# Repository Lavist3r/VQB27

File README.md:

# VQB27
Small project for controlling two seven-segment displays (VQB27) with an Arduino Nano.

# About VQB27

This project utilizes two VQB27 seven-segment displays. Information on the VQB27 is really tight, only thing know about it is that it was manufactured in the GDR.

# Introduction

The VQB27, a SS126 NPN and an Arduino Nano were used in  this project. A custom PCB was designed and manufactured to have a somewhat functional two digit display thats also decent looking and not like a bomb on a breadboard.

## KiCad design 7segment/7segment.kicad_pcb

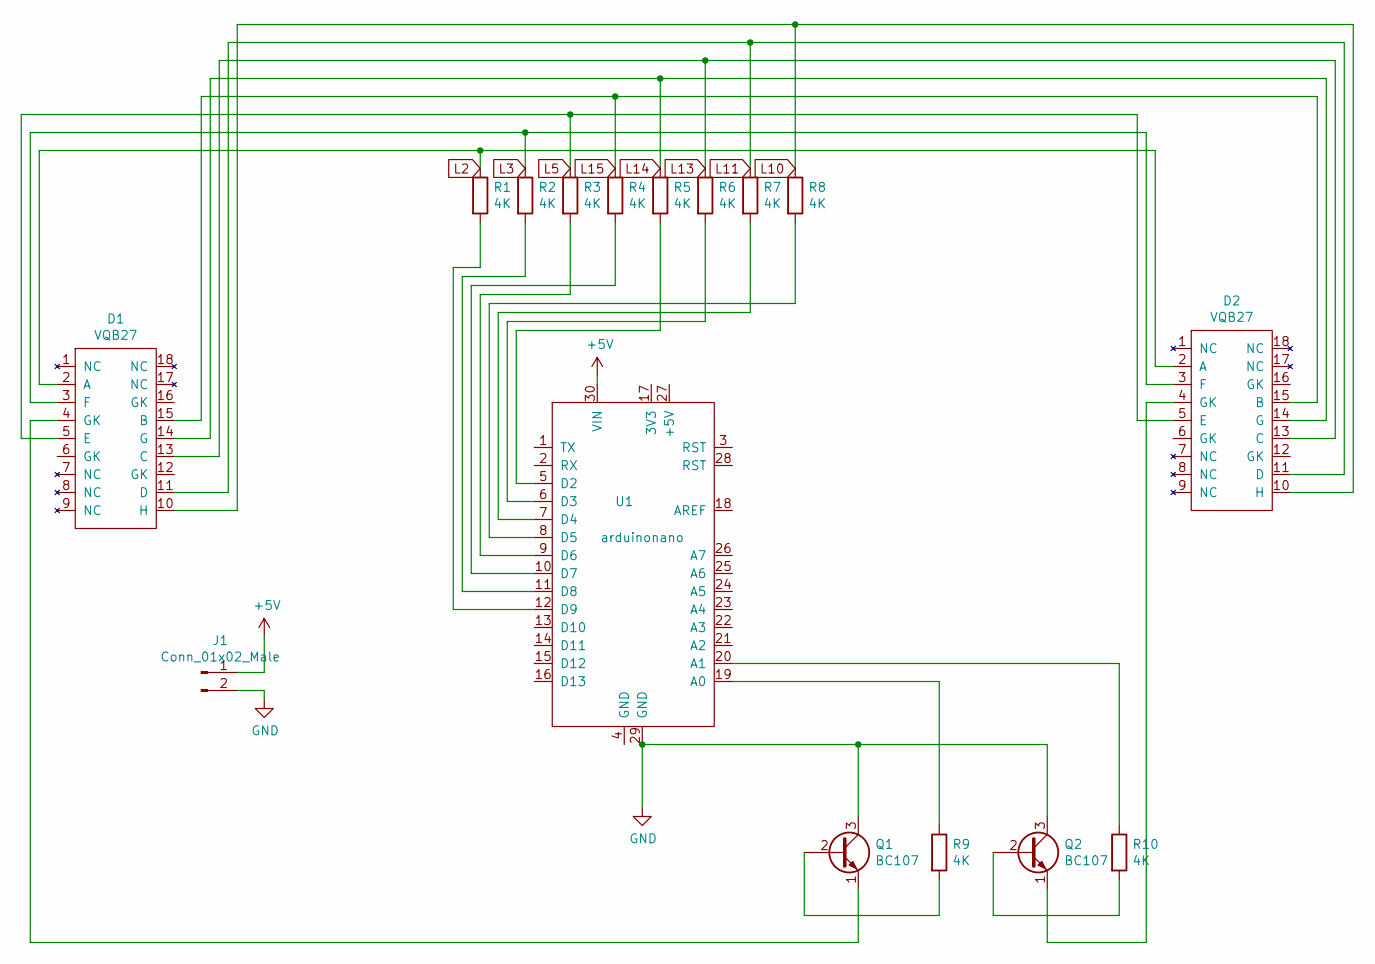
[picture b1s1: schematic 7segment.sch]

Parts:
D1, D2: VQB27
J1: Conn_01x02_Male; PinHeader_1x02_P1.00mm_Horizontal
Q1, Q2: BC107; TO-39-3
R1, R2, R3, R4, R5, R6, R7, R8, R9, R10: 4K; R_Axial_DIN0207_L6.3mm_D2.5mm_P2.54mm_Vertical
U1: arduinonano; Arduino_Nano

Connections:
+5V: J1.1, U1.30 (VIN)
GND: J1.2, Q1.3 (C), Q2.3 (C), U1.29 (GND)
L2: D1.2 (A), D2.2 (A), R1.1
L3: D1.3 (F), D2.3 (F), R2.1
L5: D1.5 (E), D2.5 (E), R3.1
L10: D1.10 (H), D2.10 (H), R8.1
L11: D1.11 (D), D2.11 (D), R7.1
L13: D1.13 (C), D2.13 (C), R6.1
L14: D1.14 (G), D2.14 (G), R5.1
L15: D1.15 (B), D2.15 (B), R4.1
unnamed: D1.4 (GK), Q1.1 (E)
unnamed: D2.4 (GK), Q2.1 (E)
unnamed: Q1.2 (B), R9.2
unnamed: Q2.2 (B), R10.2
unnamed: R1.2, U1.12 (D9)
unnamed: R2.2, U1.11 (D8)
unnamed: R3.2, U1.9 (D6)
unnamed: R4.2, U1.10 (D7)
unnamed: R5.2, U1.5 (D2)
unnamed: R6.2, U1.6 (D3)
unnamed: R7.2, U1.7 (D4)
unnamed: R8.2, U1.8 (D5)
unnamed: R9.1, U1.19 (A0)
unnamed: R10.1, U1.20 (A1)

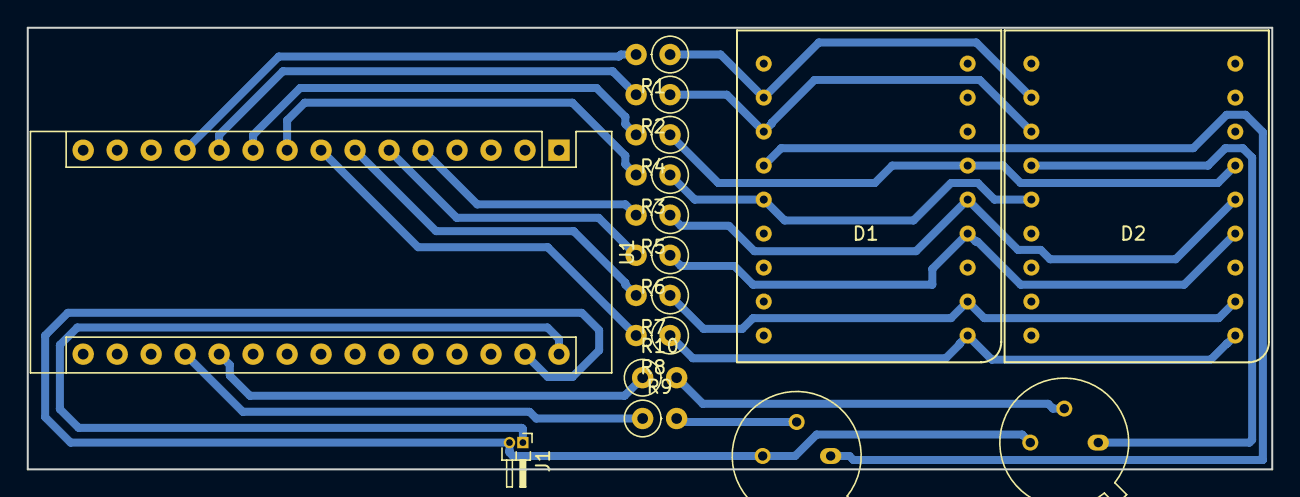
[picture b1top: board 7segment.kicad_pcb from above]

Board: 2 copper layers, 93.0 x 33.0 mm, 16 parts (0 on the bottom side), 24 nets.

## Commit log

2019-06-07 Updated-README.md
